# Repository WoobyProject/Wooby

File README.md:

# Wooby
Main repository for Wooby: Tons of Smiles

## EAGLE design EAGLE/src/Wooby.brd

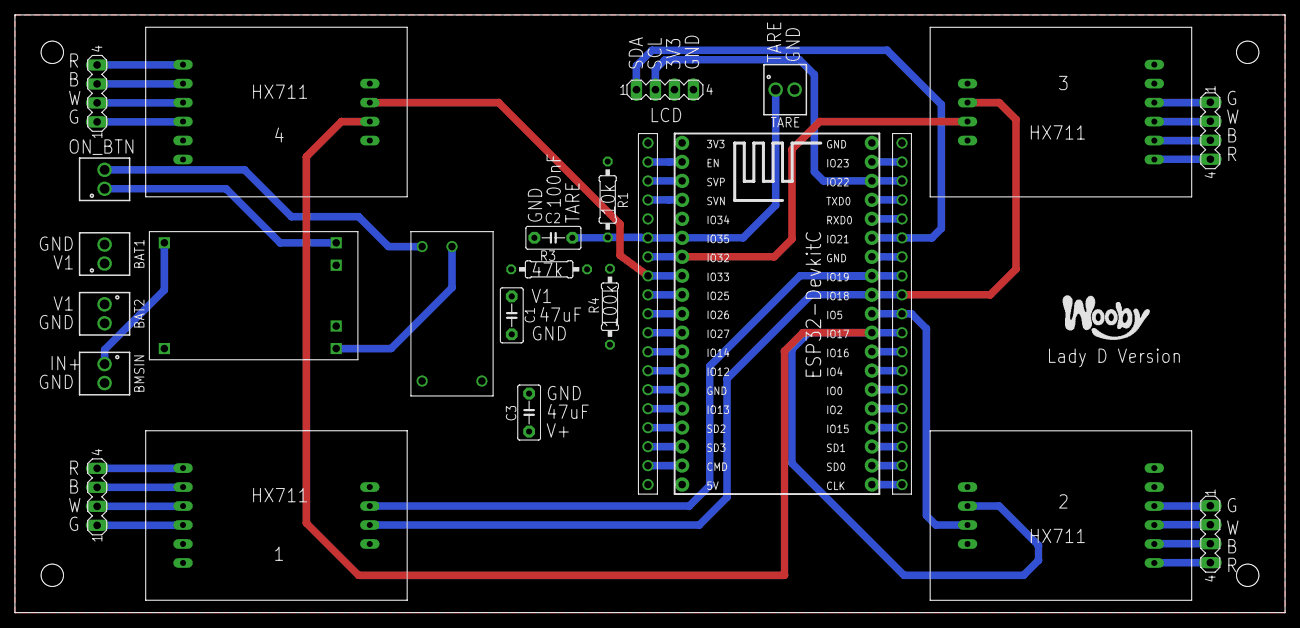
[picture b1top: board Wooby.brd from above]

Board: 2 copper layers, 170.0 x 80.0 mm, 25 parts (0 on the bottom side), 59 nets.

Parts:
BAT1, BAT2: 691210910002
BMSIN: 691210910002
C1, C2, C3: C5B3
ESP32-DEVKITC: ESP32DEVKITC; ESP32-DEVKITC
LCD: MA04-1
ON_BTN: 691210910002
R1: 5K7; 0207/10
R3, R4: 0207/10
SM1, SM2, SM3, SM4: HX711
SUC5V8V: STEPUPCONVERTOR5V8V; STEPUPCONVERTO5V8V
SV1, SV2, SV3, SV4: MA04-1
TARE: 691210910002
U$1: BMS
U$2, U$3: READER

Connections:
+3V3: ESP32-DEVKITC.1, LCD.3, R1.2, SM1.D3, SM2.D3, SM3.D3, SM4.D3, U$2.P1
BATS: ESP32-DEVKITC.5, R3.1, R4.2, U$2.P5
GND: BAT1.2, BAT2.2, BMSIN.2, C1.2, C2.2, C3.2, ESP32-DEVKITC.38, LCD.4, R4.1, SM1.D0, SM2.D0, SM3.D0, SM4.D0, SUC5V8V.OUT-, TARE.2, U$1.B-, U$1.IN-, U$3.P1
unnamed: SM1.A1, SV1.3
unnamed: SM1.A0, SV1.4
unnamed: SM1.A3, SV1.1
unnamed: SM1.A2, SV1.2
unnamed: ESP32-DEVKITC.7, SM2.D1, U$2.P7
unnamed: ESP32-DEVKITC.36, LCD.2, U$3.P3
unnamed: ESP32-DEVKITC.33, LCD.1, U$3.P6
unnamed: ESP32-DEVKITC.28, SM3.D2, SM4.D2, U$3.P11
unnamed: ESP32-DEVKITC.31, SM1.D1, U$3.P8
unnamed: ESP32-DEVKITC.30, SM1.D2, SM2.D2, U$3.P9
unnamed: ESP32-DEVKITC.8, SM3.D1, U$2.P8
unnamed: ESP32-DEVKITC.29, SM4.D1, U$3.P10
unnamed: SM4.A0, SV4.4
unnamed: SM4.A1, SV4.3
unnamed: SM4.A2, SV4.2
unnamed: SM4.A3, SV4.1
unnamed: SM3.A0, SV3.4
unnamed: SM3.A1, SV3.3
unnamed: SM3.A2, SV3.2
unnamed: SM3.A3, SV3.1
unnamed: SM2.A0, SV2.4
unnamed: SM2.A1, SV2.3
unnamed: SM2.A2, SV2.2
unnamed: SM2.A3, SV2.1
unnamed: SUC5V8V.IN-, U$1.OUT-
unnamed: ON_BTN.1, U$1.OUT+
unnamed: BMSIN.1, U$1.IN+
unnamed: ESP32-DEVKITC.18, U$2.P18
unnamed: ESP32-DEVKITC.17, U$2.P17
unnamed: ESP32-DEVKITC.16, U$2.P16
unnamed: ESP32-DEVKITC.15, U$2.P15
unnamed: ESP32-DEVKITC.14, U$2.P14
unnamed: ESP32-DEVKITC.13, U$2.P13
unnamed: ESP32-DEVKITC.12, U$2.P12
unnamed: ESP32-DEVKITC.11, U$2.P11
unnamed: ESP32-DEVKITC.10, U$2.P10
unnamed: ESP32-DEVKITC.9, U$2.P9
unnamed: ESP32-DEVKITC.4, U$2.P4
unnamed: ESP32-DEVKITC.3, U$2.P3
unnamed: ESP32-DEVKITC.2, U$2.P2
unnamed: ESP32-DEVKITC.20, U$3.P19
unnamed: ESP32-DEVKITC.21, U$3.P18
unnamed: ESP32-DEVKITC.22, U$3.P17
unnamed: ESP32-DEVKITC.23, U$3.P16
unnamed: ESP32-DEVKITC.24, U$3.P15
unnamed: ESP32-DEVKITC.25, U$3.P14
unnamed: ESP32-DEVKITC.26, U$3.P13
unnamed: ESP32-DEVKITC.27, U$3.P12
unnamed: ESP32-DEVKITC.32, U$3.P7
unnamed: ESP32-DEVKITC.34, U$3.P5
unnamed: ESP32-DEVKITC.35, U$3.P4
unnamed: ON_BTN.2, SUC5V8V.IN+
unnamed: ESP32-DEVKITC.37, U$3.P2
TARE: C2.1, ESP32-DEVKITC.6, R1.1, TARE.1, U$2.P6
V1: BAT1.1, BAT2.1, C1.1, R3.2, U$1.B+
V+: C3.1, ESP32-DEVKITC.19, SUC5V8V.OUT+, U$2.P19

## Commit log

2020-10-14 update of the repository with all the main streams
2020-10-14 Remove .DS_Store from everywhere
2020-10-14 Organizing the 3d designs
2020-10-14 Adding the .gitattributes
2020-10-14 A new .gitattributes
2020-10-14 Changes on the Python code
2020-10-20 [EAGLE] Schematic first version
2020-10-22 Several changes
    - Changes on the embedded code
    - Changes on the Python codes
    - New data sets
    - Changes to the Python lib
2020-11-01 [PCB] Size 106mm x 40mm with terminal blocks 5mm, 2 pins.
2020-11-06 [PCB] Version 1
2020-11-10 Updates on the Python code and the embedded code
    Everything on the title.
2020-12-06 Changes on several folders
    EAGLE:
    Small change to name the inputs of the HX711
    ESP32:
    Update with latest code with Bluetooth (not working). A cleaning will be done to make it work.
    Python:
    Latest code with the library and new datasets.
2020-12-08 Wooby with Bluetooth!
    Bluetooth functionality plus some corrections to the BF_XXX and B_XXX booleans
2020-12-15 Latest version for sending the prototype
2020-12-21 Latest changes for dev
    Almost ready to be sent!!
2021-02-01 Changes on the Python code and on the embedded code
    Embedded code: change of the threshold for filtering
    Python:
    - Improvement of the filtering tests
    - Creation of a test base for clustering
2021-02-16 Release version 1 just before shipping!
2021-05-30 Rename scale as scale1
2021-06-13 Adding one HX711 sensor
2021-06-13 Creating mpu6050 source code and header
2021-06-17 Add U8g2 library to platformio.ini
2021-06-21 2nd HX711 connected to pins 12 & 14
2021-06-25 Correction of compiler/linker errors
2021-06-26 Creating battery source code and header Compilation and link passed
2021-06-26 Adding battery source code and header
2021-06-27 Creating display source code and header WoobyWifi: addinf "extern" for getIp in header battery: adding global variable BF_VCCMNG main: adding global variable and functions
2021-06-27 Creating serial communication source code and header
2021-06-29 Update of 3d desigg, Eagle and some embedded code uptades
2021-07-04 Creating weight source code and header
2021-07-04 Creating tare source code and header
2021-07-04 Creating telnet_com source code and header
2021-07-04 Creating http_com source code and header
2021-07-04 Creating bluetooth_com source code and header
2021-07-13 Changing pins to connect to both HX711 HX711 #1 CLK = 18 DOUT = 19 HX711 #2 CLK = 14 DOUT = 27
2021-07-13 Creating inactivity source code and header
2021-07-13 Moving myTare function from main.cpp to tare.cpp
2021-07-13 Moving data TEMPREF from main.cpp to tare.cpp
2021-07-13 Cleaning main.h
2021-07-13 Removing unused data and function in main.cpp
2021-07-13 Moving HX711 scale data from main.cpp to weight.cpp
2021-10-11 Update of Python code
    Update of Python code
2021-10-12 Update on Python code and datasets
    Update on Python code and datasets
2021-10-27 New data sets !
    New data sets !
2021-11-03 New measures
2021-11-04 Update of the reading code and training
    Update of the reading code and training
2021-11-04 Update of the reading and training code
    Update of the reading and training code
2021-11-04 Update training
2021-11-04 Plots
2021-11-08 Update training algo
2021-12-02 New measures for 3kg with polynomial interpolation
2021-12-06 Adding equation to calculate weight in grams using both sensors value without unit
2022-05-01 Branch for development of 4 HX711
2022-05-01 Correct DOUT pin for sensor #2 in _main.cpp_.
2022-06-16 Change the size of genericJSON (2000 bytes) Add delay of 100ms between 4 sensor acquisitions
2022-06-16 Rename branch Quad_HX711 -> Multi_HX711
2022-06-16 Change from 4 to 3 HX711 sensors
2022-09-08 Improve declaration of filterWeight using NB_HX711 define instead of constant
2022-09-08 Rename directory DualHX711 to MultiHX711 Add reading of serial in real time
2022-12-14 Change of order of sensors because 2 sensors have the same clock input Streamline use of HX711 library: - offset is obtained from tare - call of HX711 begin with gain Correct computation of realValue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
2022-12-16 Change real time reading to allow the reading of the 3 sensors
2022-12-20 Triple load sensor code and data
2023-01-19 Measures 1kg, 3kg and 5kg
2023-01-25 Commit with new model for Triple load cell (training with 1 to 5 kg)
2023-01-26 Adding test dataset from 200g to 10kg in directory WoobyTripleHX711ForTest
2023-02-01 Empty scale measurement and new training
2023-02-01 Small update
2023-02-01 New model 0 to 5 kg
2023-02-02 Adding dataset in directory WoobyTripleHX711ForTest2, from 200g to 6932g
2023-02-02 Adding new dataset in directory WoobyTripleHX711ForTest2, from 200g to 6932g
2023-02-02 Correct errors (2g) on weight from 5kg to 10kg for the dataset filenames in directory WoobyTripleHX711ForTest
2023-02-09 Update of soft and measures
2023-02-14 Adding dataset in directory WoobyTripleHX711ForTest2, above 7923g and 0g
2023-02-14 New model training and export
2023-02-21 Modification of triggering the filtering New weight calculation based on ML algorithm Changing the font for weight display and "grams"
2023-03-14 EagleV2
    With some improvements since the first V" printed version, but still with some improvements to be performed
2023-04-05 ON_BTN insertion on circuit and board
2023-04-05 Resistance values written on board
2023-04-10 Remove the MPU
2023-04-10 Remove the MPU (2)
2023-04-11 Modification of TYPE 0 (PROTOTYPE) Changing to TYPE 0 When TYPE 3, if debug mode is activated, then inactivity check is disabled Update of calibration parameters to reset values
2023-04-12 Adding Hold function Hold happens when weight does not change for 10 seconds Display shows "OK" on left bottom corner
2023-04-13 Confirmation time for Hold changed to 5s Tare button pushed during 500ms stops the Hold Adjust position of "OK" for Hold Correct condition to trigger Hold
2023-04-20 Calibration dataset in directory WoobyTripleHX711ForTest3 with the first printed prototype (pink and blue)
2023-04-30 Multiples changes
    - Changes on the code for comparing the wood and the Eraser training.
    - Supplementary changes to the pyWooby library to make everything more modular and be able to run batches of analysis.
    - Reorganization of old code.
2023-05-28 Add a flag to enable/disable a sensor. When a sensor is disabled, the initialization, the tare and the continuous reading are not done. To enable/disable, change the boolean in constant table HX711_c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
2023-06-20 Adding measurement from 0 to 10kg with 4 sensors
2023-06-27 New measurements for 4 sensors Wooby
2023-06-29 Adding measurements at 500g and 10.410kg
2023-07-02 Commit with the new models for Quad Wooby
2023-07-02 Commit for changes on the model for QuadWooby
2023-07-02 Update pyWooby cache
2023-07-06 Activation of all 4 sensors New calibrations coeffs based on additional measurements at 500gr and 10.410kg
2023-07-06 Adding measurements for 1.493kg and 2.481kg
2023-08-03 Measurements with Vader prototype
2023-08-14 Calibration for Vader: - first order (default) - third order
2023-10-17 Update of the calibration for Vader v1
2023-10-17 Updates to the Vcc analysis
2023-10-19 Update to read external files for Vcc analysis
2023-10-19 Add the filtered Vcc
2023-10-24 Update for newest charge curves
    Congrats to all the team! Amazing autonomy !
2023-11-01 Measurements for Vader2
2023-11-05 Updates for new Vcc analysis and new measures for Vader2
2023-11-28 Adding measurements for Spidey: - conf 1a : 4 screws, software filtering on - conf 1b : 2 screws, software filtering on - conf 2a : 4 screws, software filtering off - conf 2b : 2 screws, software fil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
2024-01-16 Lady D Version
2024-01-23 Adding measures with Spidey in directory WoobyQuadHX711ForSpidey2
2024-02-08 Adding characterization of 4 sensors used in Spidey prototype. Capture text files (capture from USB) are in sub-directories (1, 2, 3, 4) of Python\datasets\SensorCharacterization.
2024-02-10 Changes for Spidey
2024-02-27 Latest changes
2024-02-27 Comment out the print for file reading
2024-02-27 Update for the torsion study
2024-03-05 Changes for Spidey and Vader
2024-03-05 Adding measures with Beattle Each sensor calibrated alone
2024-03-05 Commit python scripts
2024-04-04 Several changes for calibration
2024-04-04 Adding Beetle Calibration Run #1 : weight at the centre Run #2 : weight on sensor #1 Run #3 : weight on sensor #2 Run #4 : weight on sensor #3 Run #5 : weight on sensor #4
2024-04-11 Adding measurements for Beetle in directory WoobyQuadHX711ForBeetle2
2024-05-06 Adding measurents in directory WoobyQuadHX711ForBeetlePosition
2024-05-28 Update of new datasets and new functions for reading and processing data
2024-06-09 Calibrated computation of weight Correction of tare button declaration (-> internal pull up) Update of coefficients for VCC measurement
2024-06-20 Updated version of the analysis for baby measures and new baby measurements
2024-06-30 New data from the 3D pieces addition to Beetle
    New data from the 3D pieces addition to Beetle and changes to the library to better read and plot this data
2024-08-08 Measures with latest prototype of X Wooby
2024-08-13 New mesures in directory WoobyQuadHX711ForX, data in files Position3
2024-08-13 New training models for the X configuration
2024-09-17 Modifications: - only 1 acquisition per sensor - tare button confirmation time set to 200ms - change of the coefficients News: - managing the display with a state machine (function measuringSequence)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
2024-09-18 - renaming some variables - removing unused variables - changing bSync threshold to 300g - adding moving average for the final weight - moving average window set to 5
2024-09-19 Use the standard deviation in the state machine for display Remove the BDEF_HOLD define Note: only the tare button can allow a new measurement
2024-09-26 - changing the sequencing of sensors reading: 100ms between S2 and S3, 200ms between S4 and S1 - moving average of relative values reset during tare - bug correction in JSON build (stack panic) - cha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
2024-10-16 - inactivity time set to 10 minuntes - Coeff to convert VCC from ESP32 voltage to battery voltage modified - in display state 1, reset the time out if weight changes for more than +/- 300gr
